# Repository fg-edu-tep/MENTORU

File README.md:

# MENTORU

Sistema de monitoreo biométrico distribuido basado en ESP32. Varios dispositivos vestibles (reloj, gafas, pecho, sensor GSR) miden señales fisiológicas y de movimiento, y las transmiten de forma inalámbrica por **ESP-NOW** a un receptor central que las expone como JSON vía HTTP.

Proyecto de la asignatura *Fundamentos de Electrónica* (Universidad de los Andes).

## Arquitectura

Cada dispositivo sensor transmite tramas de tamaño fijo (88 bytes) usando el protocolo propio **ESB-P** (*ESP-NOW Sensor Broadcast Protocol*, ver [`ESB-P_ESP-NOW SENSOR BROADCAST PROTOCOL DRAFT 1.pdf`](<./ESB-P_  ESP-NOW SENSOR BROADCAST PROTOCOL           DRAFT 1.pdf>)). Cada trama tiene:

```c
typedef struct __attribute__((packed)) {
  char    deviceId[16];      // identifica el dispositivo
  char    broadcastType[16]; // tipo de dato: FORM, HR, VMEDIDO, ACCEL, FLEX...
  uint8_t payload[56];       // datos específicos de cada tipo
} espMessage;
```

Un único receptor ESP32 escucha todas las tramas, agrupa por `deviceId` + `broadcastType`, y sirve el último valor de cada uno en `GET /devices` como JSON.

## Dispositivos

| Carpeta | Dispositivo | Descripción |
|---|---|---|
| [`MasterReciever/`](MasterReciever) | Receptor | Proyecto PlatformIO (ESP32-S3). SoftAP + ESP-NOW, sirve `/devices`. Incluye además un sensor "Vest" propio a bordo (MPU-6050 + flex) que se muestrea localmente. |
| [`Wk/`](Wk) | Reloj | Pantalla LCD redonda + touch (CST816S) + sensor de ritmo cardíaco MAX30102, interfaz LVGL con asistente de formulario. Transmite `FORM` y `HR`. |
| [`Arduino/GSR/`](Arduino/GSR) | Sensor GSR | Lee la respuesta galvánica de la piel por ADC y transmite `VMEDIDO`. |
| [`GSR sensor/`](GSR%20sensor) | Sensor GSR (PCB) | Diseño KiCad del PCB del sensor GSR, con archivos de fabricación (gerbers). |
| [`PCB_Gafas/`](PCB_Gafas) | Gafas | Diseño KiCad del PCB del dispositivo de gafas (acelerómetro, `ACCEL`). |
| [`PCB_Pecho/`](PCB_Pecho) | Pecho | Diseño KiCad del PCB del dispositivo de pecho (acelerómetro + flex, `ACCEL`/`FLEX`). |
| [`Fuente Fundamentos/`](<Fuente Fundamentos>) · [`PCB_Fuente/`](PCB_Fuente) | Fuente de alimentación | Diseño de la fuente/boost converter (Altium y KiCad respectivamente). |
| [`Arduino/ESP32RECEPTORA/`](Arduino/ESP32RECEPTORA) | Receptor (versión anterior) | Primera versión del receptor, solo maneja Reloj (`FORM`/`HR`) y GSR (`VMEDIDO`). Reemplazada por `MasterReciever/`. |

## Hardware / PCBs (KiCad)

`KiCad_FootPrints/` contiene las librerías de footprints y símbolos usadas por los diseños anteriores:

- `usini_kicad_sensors-main/` — librería de sensores I2C de terceros (ADXL345, BMP180, MPL3115A2, PAJ7620, SI7021, TSL2561, INA219, BH1750, BME280/680, MAX30102, MPU6050, VL53L0X, MLX90614, conector de audio TRRS).
- `XIAO_ESP32C3-main/` — símbolo/footprint del módulo Seeed XIAO ESP32C3.
- `ESP32-S3/`, `BoostConverter/`, `CostumFuse/`, `Transformer/` — footprints propios adicionales.

## Compilar y flashear

- **`MasterReciever/`** — proyecto PlatformIO, board `esp32-s3-devkitc-1`, framework Arduino. Compilar con `pio run` o desde la extensión de PlatformIO.
- **`Wk/`** (`Wk.ino`) y **`Arduino/*/`** — sketches de Arduino IDE, requieren el core de ESP32 y las librerías `lvgl`, `TFT_eSPI`, `MAX30105`/`heartRate`, `esp_now`.

## Documentación

- [`ESB-P_ESP-NOW SENSOR BROADCAST PROTOCOL DRAFT 1.pdf`](<./ESB-P_  ESP-NOW SENSOR BROADCAST PROTOCOL           DRAFT 1.pdf>) — especificación del protocolo de comunicación entre dispositivos y receptor.
- [`Informe_Final.pdf`](Informe_Final.pdf) — informe final del proyecto.

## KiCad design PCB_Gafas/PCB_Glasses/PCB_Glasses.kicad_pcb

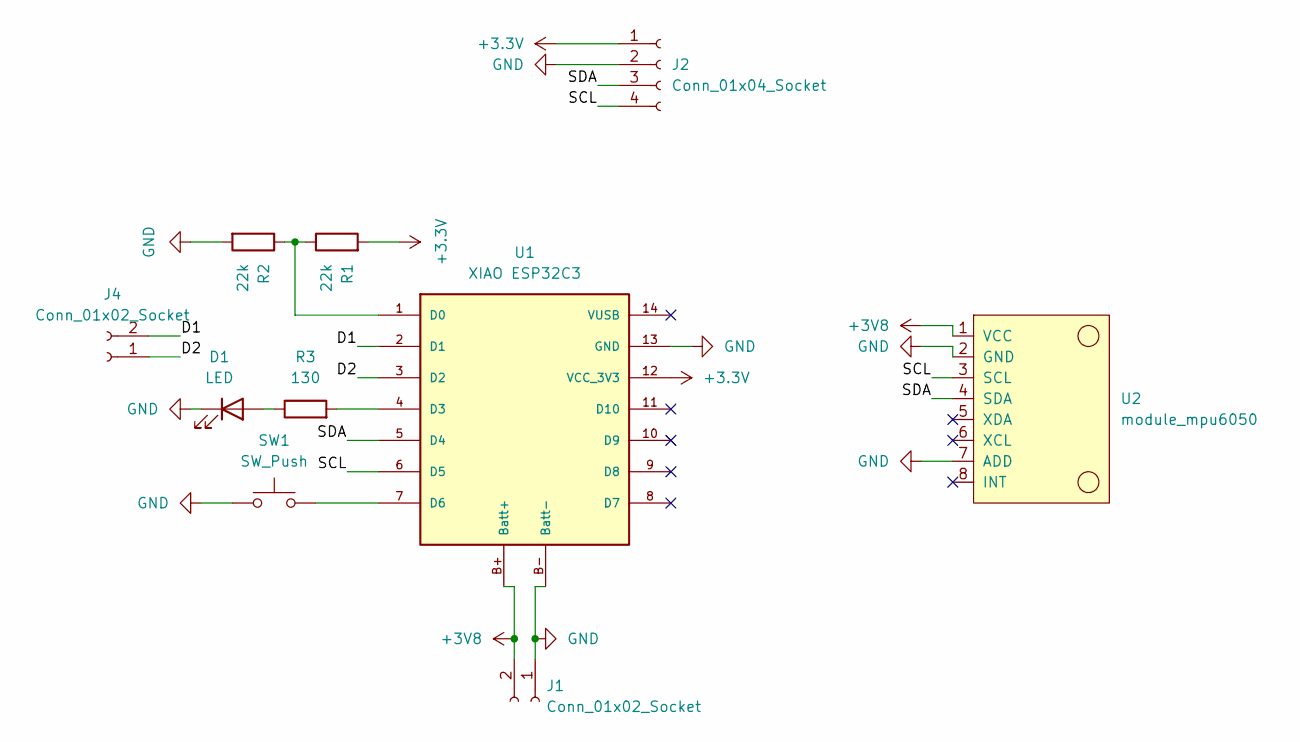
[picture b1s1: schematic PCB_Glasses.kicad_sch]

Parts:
D1: LED; LED_0805_2012Metric
J1, J4: Conn_01x02_Socket; JST_EH_B2B-EH-A_1x02_P2.50mm_Vertical
J2: Conn_01x04_Socket; JST_EH_B4B-EH-A_1x04_P2.50mm_Vertical
R1, R2: 22k; R_1206_3216Metric_Pad1.30x1.75mm_HandSolder
R3: 130; R_1206_3216Metric_Pad1.30x1.75mm_HandSolder
SW1: SW_Push; SW_SPST_CK_RS282G05A3
U1: XIAO ESP32C3; xiao_esp32c3
U2: module_mpu6050

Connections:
+3.3V: J2.1, R1.2, U1.12 (VCC_3V3)
+3V8: J1.2, U1.B+ (Batt+), U2.1 (VCC)
/D1: J4.2, U1.2 (D1)
/D2: J4.1, U1.3 (D2)
/SCL: J2.4, U1.6 (D5), U2.3 (SCL)
/SDA: J2.3, U1.5 (D4), U2.4 (SDA)
GND: D1.1 (K), J1.1, J2.2, R2.2, SW1.1, U1.13 (GND), U1.B- (Batt-), U2.2 (GND), U2.7 (ADD)
unnamed: D1.2 (A), R3.1
unnamed: R1.1, R2.1, U1.1 (D0)
unnamed: R3.2, U1.4 (D3)
unnamed: SW1.2, U1.7 (D6)

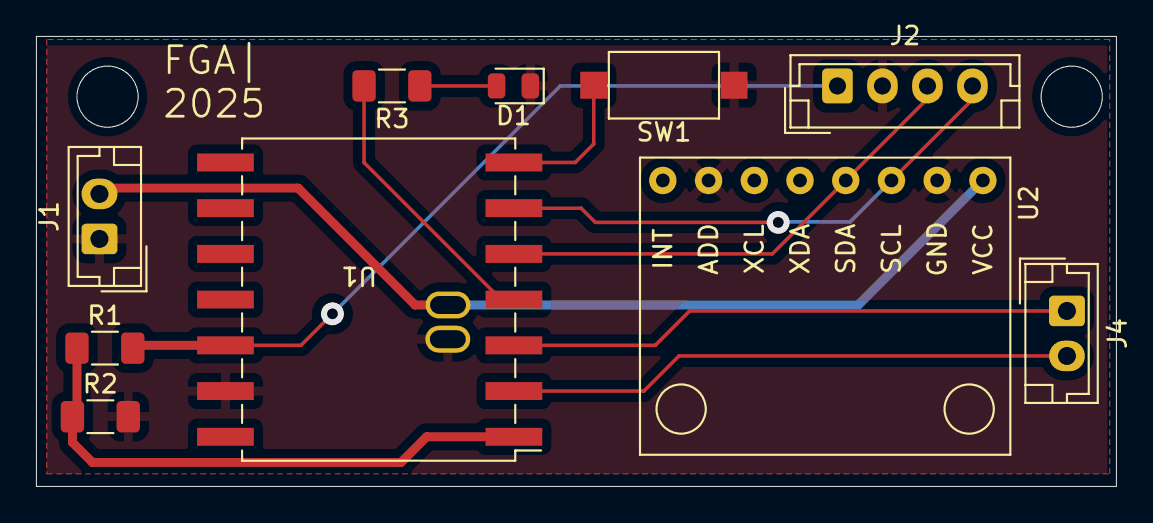
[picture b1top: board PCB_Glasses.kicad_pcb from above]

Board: 2 copper layers, 60.0 x 25.0 mm, 10 parts (0 on the bottom side), 11 nets.

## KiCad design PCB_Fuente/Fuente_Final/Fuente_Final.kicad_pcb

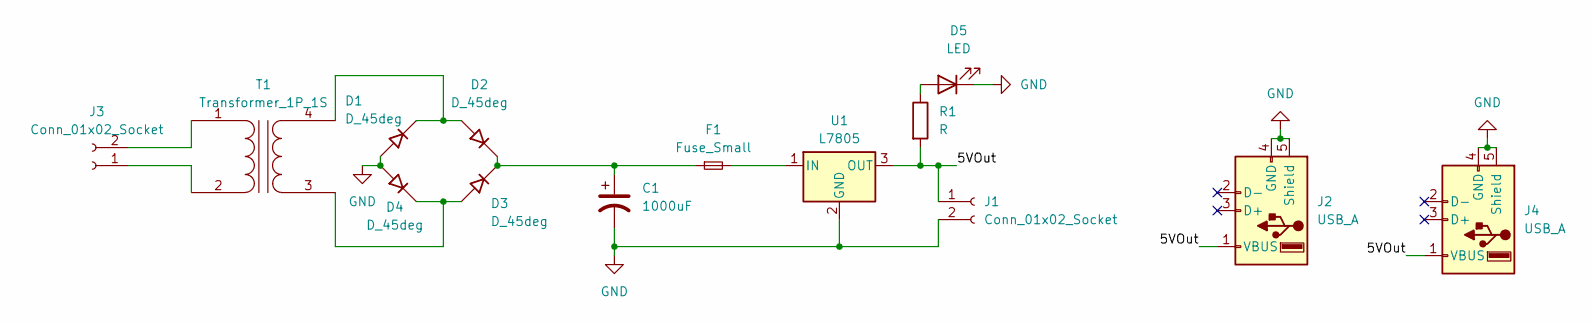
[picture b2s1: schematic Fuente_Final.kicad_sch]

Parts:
C1: 1000uF; CP_Radial_D10.0mm_P5.00mm
D1, D3: D_45deg; D_DO-15_P5.08mm_Vertical_AnodeUp
D2, D4: D_45deg; D_DO-15_P5.08mm_Vertical_KathodeUp
D5: LED; LED_0805_2012Metric_Pad1.15x1.40mm_HandSolder
F1: Fuse_Small; Fuse_MF-SMDF200-2_Custom
J1: Conn_01x02_Socket; JST_EH_B2B-EH-A_1x02_P2.50mm_Vertical
J2, J4: USB_A; USB_A_Receptacle_GCT_USB1046
J3: Conn_01x02_Socket; TerminalBlock_bornier-2_P5.08mm
R1: R; R_0805_2012Metric_Pad1.20x1.40mm_HandSolder
T1: Transformer_1P_1S; THT_10mm_Transformer
U1: L7805; TO-220-3_Vertical

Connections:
/5VOut: J1.1, J2.1 (VBUS), J4.1 (VBUS), R1.2, U1.3 (OUT)
GND: C1.2, D1.2 (A), D4.2 (A), D5.1 (K), J1.2, J2.4 (GND), J2.5 (Shield), J4.4 (GND), J4.5 (Shield), U1.2 (GND)
unnamed: D1.1 (K), D2.2 (A), T1.4 (SB)
unnamed: C1.1, D2.1 (K), D3.1 (K), F1.1
unnamed: D3.2 (A), D4.1 (K), T1.3 (SA)
unnamed: D5.2 (A), R1.1
unnamed: J3.1, T1.2 (AB)
unnamed: J3.2, T1.1 (AA)
unnamed: F1.2, U1.1 (IN)

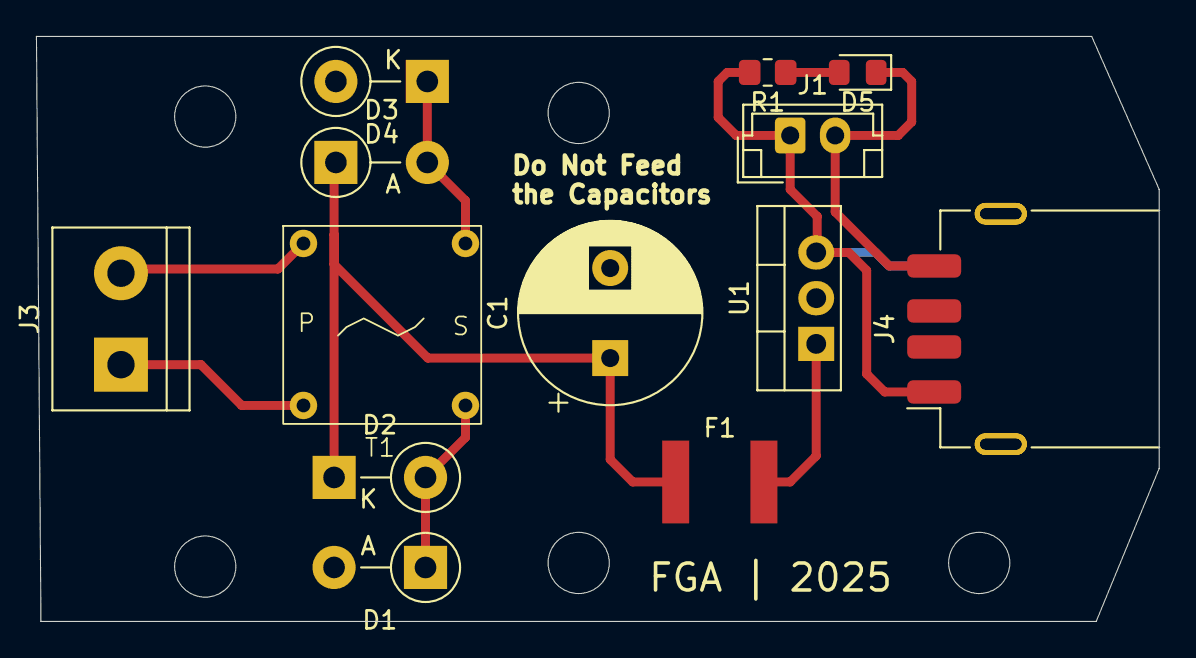
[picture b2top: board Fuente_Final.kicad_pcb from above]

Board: 2 copper layers, 62.4 x 32.5 mm, 14 parts (1 on the bottom side), 9 nets.

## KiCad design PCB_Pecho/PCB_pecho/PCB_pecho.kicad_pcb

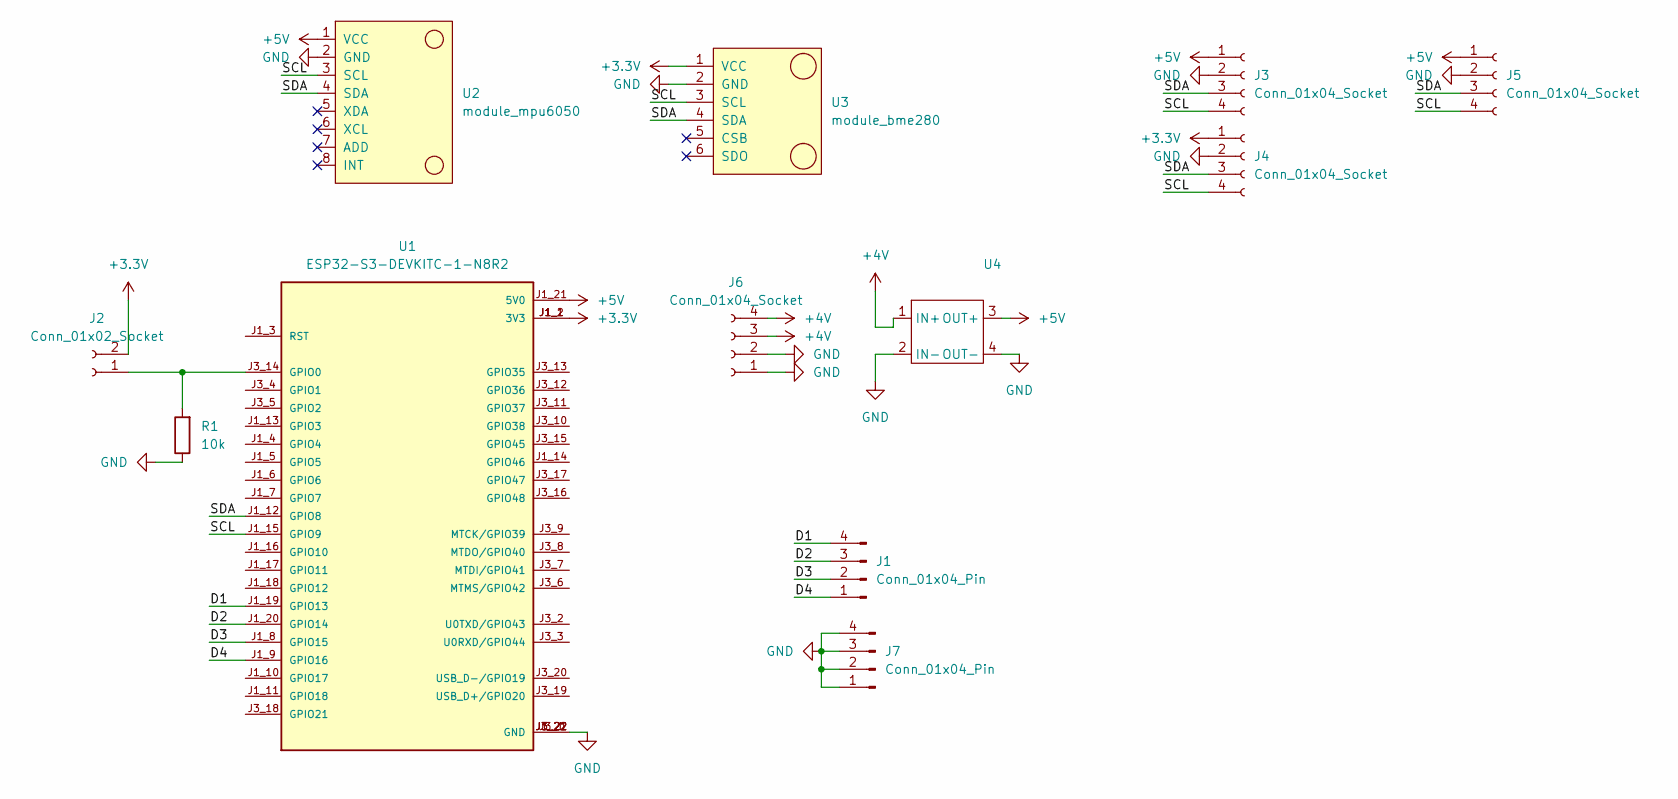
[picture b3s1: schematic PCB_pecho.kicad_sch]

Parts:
J1, J7: Conn_01x04_Pin; JST_EH_B4B-EH-A_1x04_P2.50mm_Vertical
J2: Conn_01x02_Socket; JST_EH_B2B-EH-A_1x02_P2.50mm_Vertical
J3, J4, J5, J6: Conn_01x04_Socket; JST_EH_B4B-EH-A_1x04_P2.50mm_Vertical
R1: 10k; R_1206_3216Metric_Pad1.30x1.75mm_HandSolder
U1: ESP32-S3-DEVKITC-1-N8R2; XCVR_ESP32-S3-DEVKITC-1-N8R2; PARTREV V1
U2: module_mpu6050
U3: module_bme280
U4: (no value)

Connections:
+3.3V: J2.2, J4.1, U1.J1_1 (3V3), U1.J1_2 (3V3), U3.1 (VCC)
+4V: J6.3, J6.4, U4.1 (IN+)
+5V: J3.1, J5.1, U1.J1_21 (5V0), U2.1 (VCC), U4.3 (OUT+)
/D1: J1.4, U1.J1_19 (GPIO13)
/D2: J1.3, U1.J1_20 (GPIO14)
/D3: J1.2, U1.J1_8 (GPIO15)
/D4: J1.1, U1.J1_9 (GPIO16)
/SCL: J3.4, J4.4, J5.4, U1.J1_15 (GPIO9), U2.3 (SCL), U3.3 (SCL)
/SDA: J3.3, J4.3, J5.3, U1.J1_12 (GPIO8), U2.4 (SDA), U3.4 (SDA)
GND: J3.2, J4.2, J5.2, J6.1, J6.2, J7.1, J7.2, J7.3, J7.4, R1.1, U1.J1_22 (GND), U1.J3_1 (GND), U1.J3_21 (GND), U1.J3_22 (GND), U2.2 (GND), U3.2 (GND), U4.2 (IN-), U4.4 (OUT-)
unnamed: J2.1, R1.2, U1.J3_14 (GPIO0)

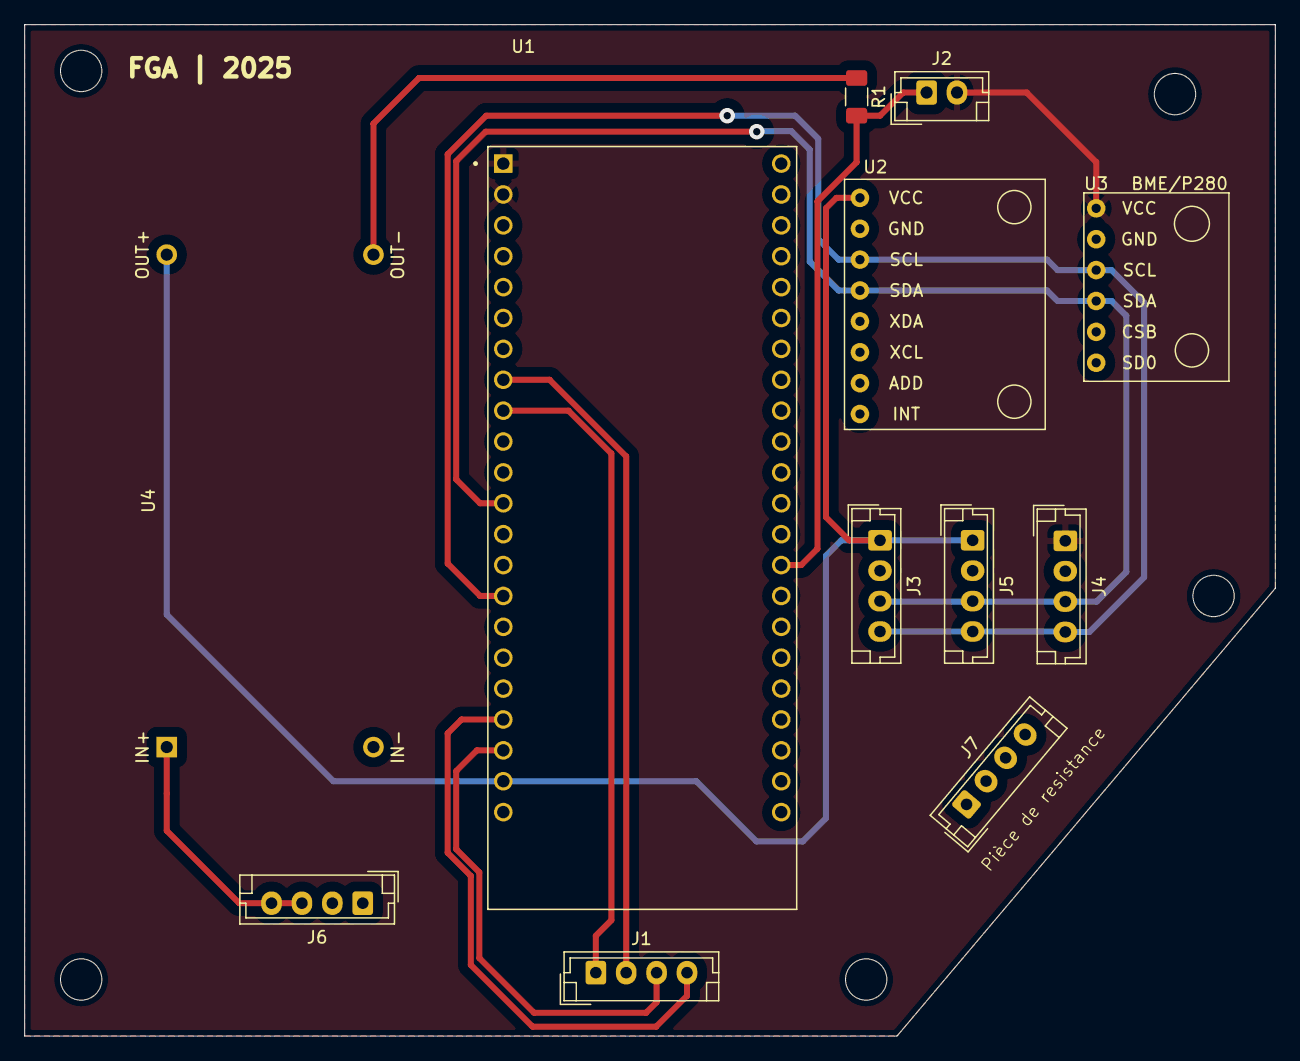
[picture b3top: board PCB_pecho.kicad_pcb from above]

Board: 2 copper layers, 102.9 x 83.2 mm, 12 parts (0 on the bottom side), 11 nets.

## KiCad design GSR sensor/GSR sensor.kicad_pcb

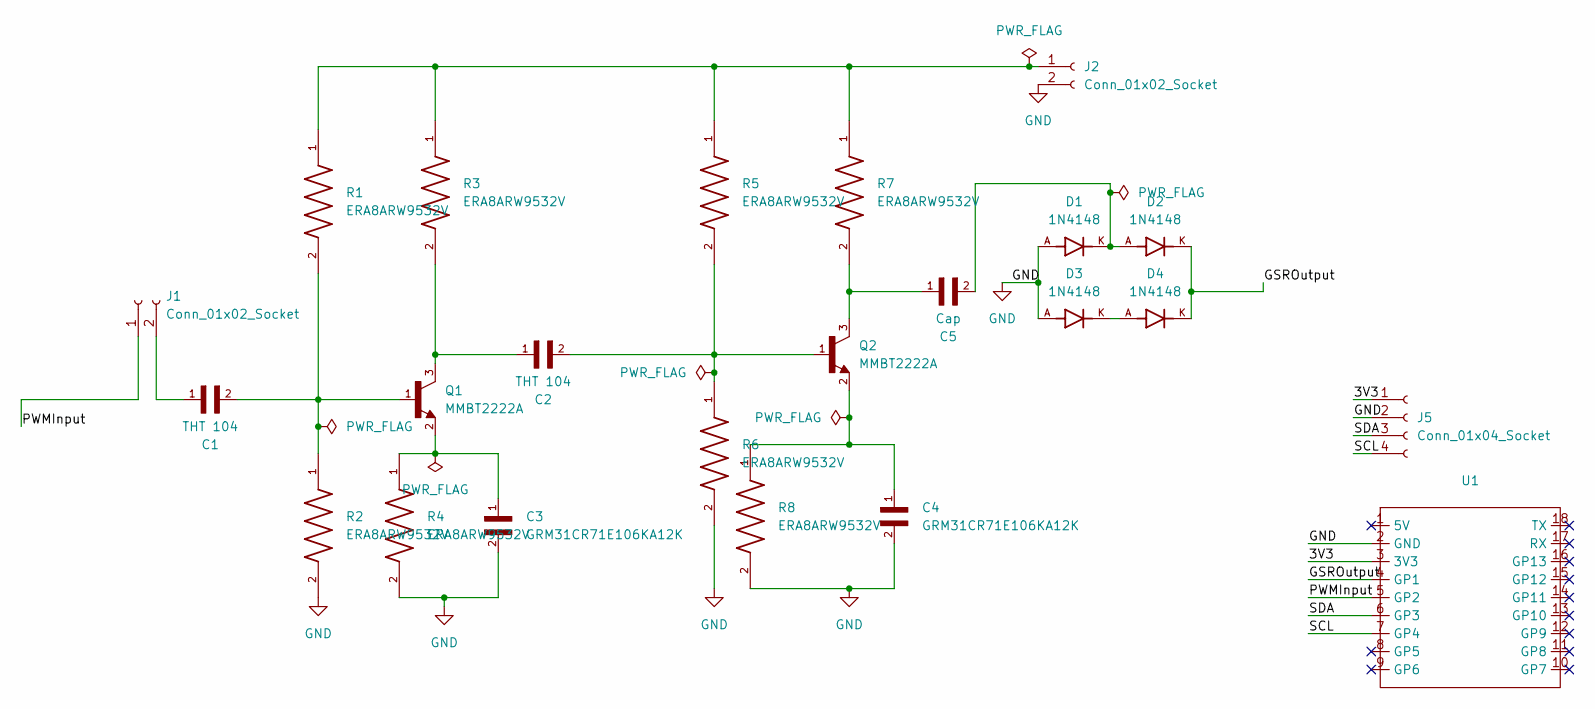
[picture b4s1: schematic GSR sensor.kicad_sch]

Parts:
C1, C2: THT 104; C_Radial_D5.0mm_H7.0mm_P2.00mm
C3, C4: GRM31CR71E106KA12K; CAPC3216X180N
C5: Cap; CAPC3216X180N
D1, D2, D3, D4: 1N4148; DIOAD753W49L380D172B; PARTREV 5
J1, J2: Conn_01x02_Socket; JST_EH_B2B-EH-A_1x02_P2.50mm_Vertical
J5: Conn_01x04_Socket; JST_EH_B4B-EH-A_1x04_P2.50mm_Vertical
Q1, Q2: MMBT2222A; SOT95P240X120-3N; PARTREV 2024-03-11
R1, R2, R3, R4, R5, R6, R7, R8: ERA8ARW9532V; RES_ERA8ARW9532V; PARTREV 3/1/2020
U1: ESP32-S3-XIAO

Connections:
/3V3: J5.1, U1.3 (3V3)
/GSROutput: D2.K, D4.K, U1.4 (GP1)
/PWMInput: J1.1, U1.5 (GP2)
/SCL: J5.4, U1.7 (GP4)
/SDA: J5.3, U1.6 (GP3)
GND: C3.2, C4.2, D1.A, D3.A, J2.2, J5.2, R2.2, R4.2, R6.2, R8.2, U1.2 (GND)
unnamed: C1.2, Q1.1, R1.2, R2.1
unnamed: C2.1, Q1.3, R3.2
unnamed: C2.2, Q2.1, R5.2, R6.1
unnamed: C3.1, Q1.2, R4.1
unnamed: C4.1, Q2.2, R8.1
unnamed: C5.1, Q2.3, R7.2
unnamed: C5.2, D1.K, D2.A
unnamed: D3.K, D4.A
unnamed: C1.1, J1.2
unnamed: J2.1, R1.1, R3.1, R5.1, R7.1

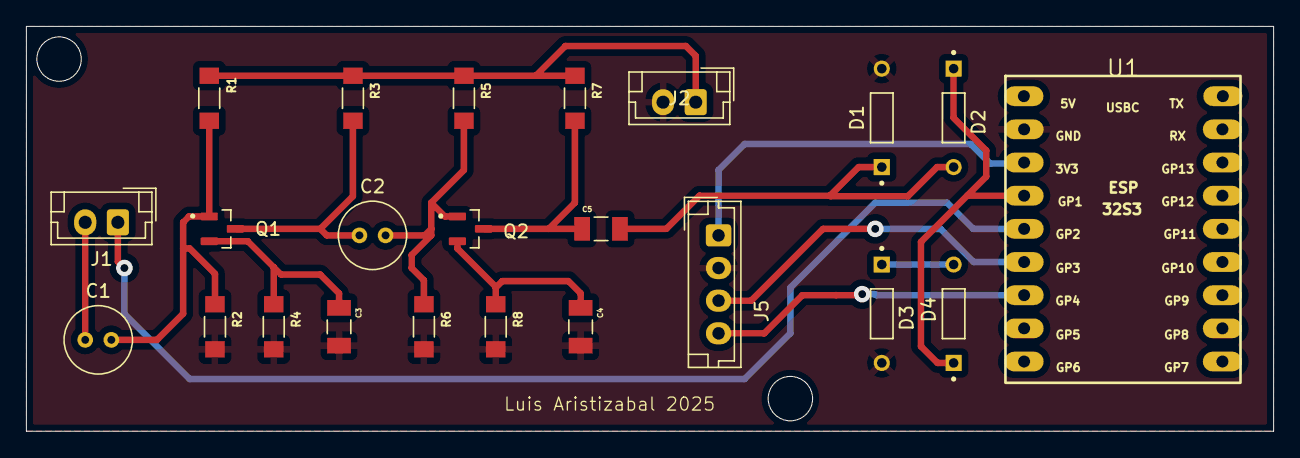
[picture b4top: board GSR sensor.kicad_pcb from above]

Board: 2 copper layers, 95.5 x 31.0 mm, 23 parts (0 on the bottom side), 16 nets.

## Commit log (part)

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2025-04-28 Sch gafas
2025-04-29 Started Gafas Routing
2025-04-29 PCB Glasses Done
2025-04-29 Cosa
2025-05-02 "Muchos Avances PBBs"
2025-05-02 cambios
2025-05-02 GSR PCB
2025-05-18 Comunicacion GSR y Pecho
2025-05-18 Cambios ESPRECEPTORA, RELOJ
2025-07-02 Finales
